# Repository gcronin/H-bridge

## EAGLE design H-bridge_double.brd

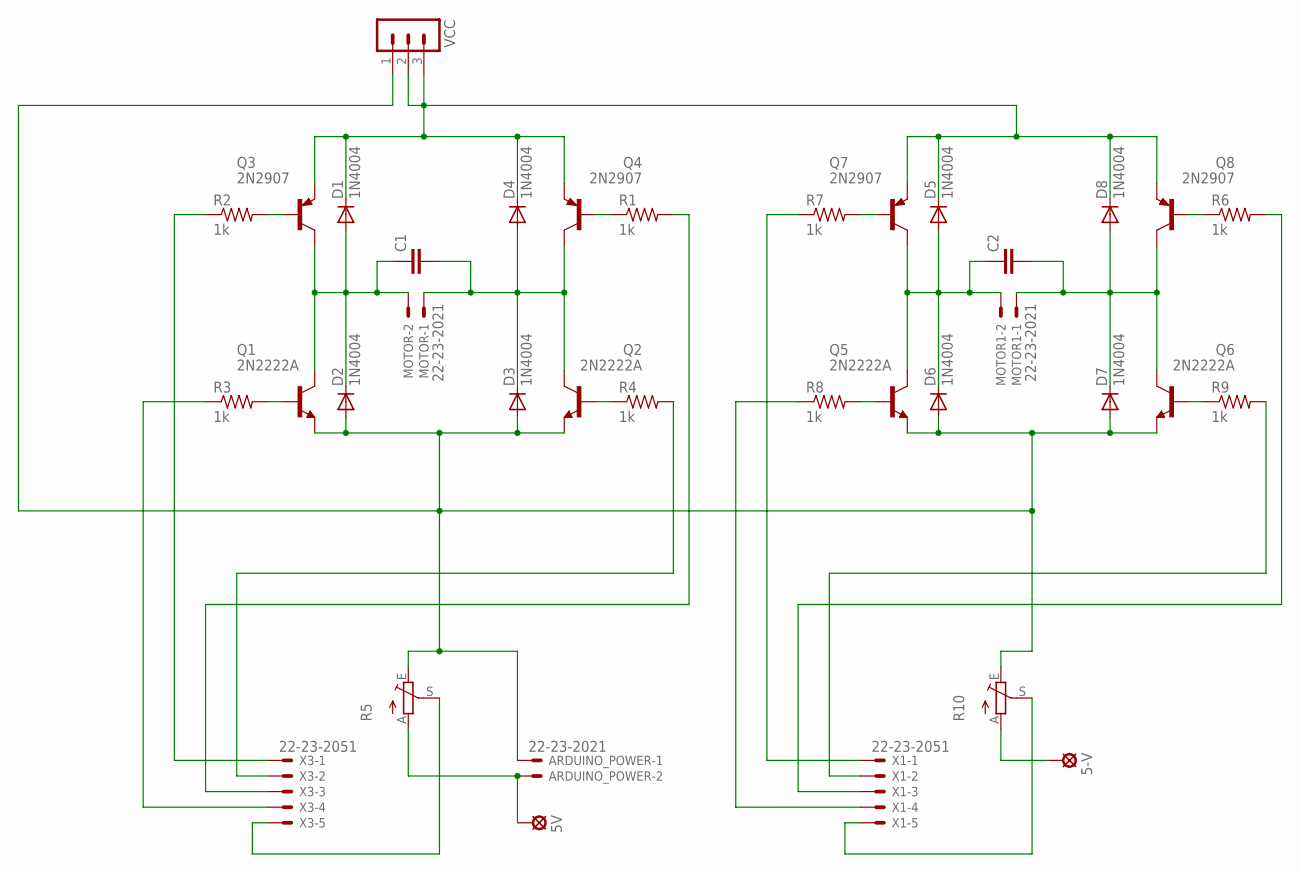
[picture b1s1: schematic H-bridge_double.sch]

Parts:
5-V, 5V: LSP10
ARDUINO_POWER: 22-23-2021
C1, C2: C2.5/2; C2.5-2
D1, D2, D3, D4, D5, D6, D7, D8: 1N4004; DO41-10
MOTOR, MOTOR1: 22-23-2021
Q1, Q2, Q5, Q6: 2N2222A; TO18
Q3, Q4, Q7, Q8: 2N2907; TO18
R1, R2, R3, R4, R6, R7, R8, R9: 1k; 0309/12
R5, R10: TRIM_EU-CA6V; CA6V
VCC: MA03-1
X1, X3: 22-23-2051

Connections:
GND: ARDUINO_POWER.1, D2.A, D3.A, D6.A, D7.A, Q1.1 (E), Q2.1 (E), Q5.1 (E), Q6.1 (E), R5.E, R10.E, VCC.1
unnamed: Q4.2 (B), R1.1
unnamed: Q2.2 (B), R4.1
unnamed: C1.2, D3.C, D4.A, MOTOR.1, Q2.3 (C), Q4.3 (C)
unnamed: Q8.2 (B), R6.1
unnamed: R3.1, X3.4
unnamed: Q6.2 (B), R9.1
unnamed: R4.2, X3.2
unnamed: C1.1, D1.A, D2.C, MOTOR.2, Q1.3 (C), Q3.3 (C)
unnamed: D1.C, D4.C, D5.C, D8.C, Q3.1 (E), Q4.1 (E), Q7.1 (E), Q8.1 (E), VCC.2, VCC.3
unnamed: Q3.2 (B), R2.2
unnamed: Q1.2 (B), R3.2
unnamed: R5.S, X3.5
unnamed: R2.1, X3.1
unnamed: R1.2, X3.3
unnamed: 5-V.MP, R10.A
unnamed: C2.2, D7.C, D8.A, MOTOR1.1, Q6.3 (C), Q8.3 (C)
unnamed: R9.2, X1.2
unnamed: C2.1, D5.A, D6.C, MOTOR1.2, Q5.3 (C), Q7.3 (C)
unnamed: 5V.MP, ARDUINO_POWER.2, R5.A
unnamed: Q7.2 (B), R7.2
unnamed: Q5.2 (B), R8.2
unnamed: R7.1, X1.1
unnamed: R8.1, X1.4
unnamed: R6.2, X1.3
unnamed: R10.S, X1.5

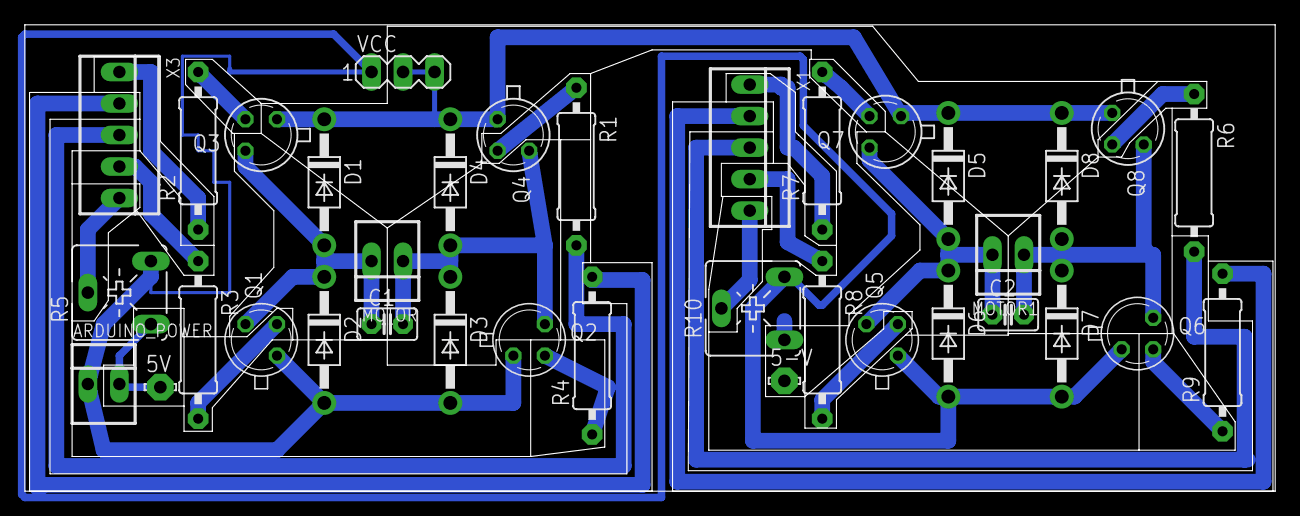
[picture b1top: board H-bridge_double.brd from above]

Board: 2 copper layers, 100.8 x 37.6 mm, 36 parts (0 on the bottom side), 26 nets.

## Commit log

2016-08-11 :boom::camel: Added .gitattributes & .gitignore files
2016-08-11 Initial Commit: Serial Controlled Direction, Pot Controlled Speed
2016-08-11 Pot controlled Direction/Power, Working
2016-08-13 Eagle CAD for Dual H-bridge
2016-08-23 Working Code for 2 H-Bridges
    Bug...need to mirror the motors so pots spin them in same direction.
2016-08-29 TransistorOnly Sketch
